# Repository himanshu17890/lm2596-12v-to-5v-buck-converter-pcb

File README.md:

# LM2596 12 V to 5 V Buck Converter PCB

A two-layer PCB for converting a 12 V DC input into a regulated 5 V DC output using an LM2596S-5 switching regulator.

## Features

- 12 V DC input through a 2-pin screw terminal
- Fixed 5 V DC output through a 2-pin screw terminal
- LM2596S-5 buck regulator
- Up to 3 A regulator rating; final usable current depends on cooling, copper area, and component ratings
- Two-layer layout with F.Cu and B.Cu ground pours
- Two M2 mounting holes and rounded board corners

## Connections

| Terminal | Pin 1 | Pin 2 |
|---|---|---|
| J3 input | IN+ / +12 V | IN- / GND |
| J4 output | OUT+ / +5 V | OUT- / GND |

Use DC input only. Do **not** connect AC mains. Confirm the output is approximately 5.0 V with a multimeter before connecting a load, and never reverse the input polarity.

## Main Components

| Reference | Component | Value / requirement |
|---|---|---|
| U1 | LM2596S-5 | Fixed 5 V buck regulator, TO-263-5 package |
| C1 | Polarized electrolytic capacitor | 680 uF, 25 V |
| C2 | Low-ESR polarized electrolytic capacitor | 220 uF, 10 V |
| L1 | Power inductor | 33 uH, at least 3 A saturation current |
| D1 | Schottky diode | 1N5824 or equivalent |
| J3, J4 | Screw terminals | 2-pin, 5.00 mm pitch |

## Project Files

Place the KiCad files in this repository root:

- `LM2596_Buck_Converter.kicad_pro`
- `LM2596_Buck_Converter.kicad_sch`
- `LM2596_Buck_Converter.kicad_pcb`

## Simulation

The design was verified in KiCad's built-in ngspice simulator using Texas Instruments' official transient SPICE model for the LM2596-5.0 (`LM2596_5P0_TRANS.LIB`, released by TI's Analog eLab Design Center), loaded via U1's Simulation Model dialog in place of a generic model.

**Setup:** 12 V input, 33 uH inductor, 220 uF output capacitor, 5 ohm (1 A) resistive load. Transient analysis, 50 ns time step, initial conditions enabled (`uic`) so the simulation starts from 0 V rather than an artificial DC operating point.

**Startup and settling — output ramps from 0 V through a stepped soft-start to ~5.0 V in about 1 ms:**

**Zoomed output ripple (3.25-3.41 ms window):**

**Results:**

- Output regulates to **~5.0 V**, matching the datasheet's 4.8-5.2 V spec at this load.
- Soft-start ramp from 0 V to regulation in **~1 ms**, matching the LM2596's internal soft-start behavior.
- With an ideal (zero-ESR) output capacitor, the loop rings at roughly 15 kHz with ~80 mV peak-to-peak swing, as shown above. Adding a realistic ESR of 0.05-0.1 ohm in series with C2 (representative of a genuine low-ESR electrolytic) damps this to **~20 mV**, confirming the datasheet's note that very low output-capacitor ESR can destabilize the feedback loop.

- 

**Model file:** [`sim/LM2596_5P0_TRANS.LIB`](sim/LM2596_5P0_TRANS.LIB)
See [`sim/SIMULATION_RESULTS.md`](sim/SIMULATION_RESULTS.md) for the full write-up, pin mapping, and settings.

> The model is TI's own release, provided "as is" with no warranty (see header comments in the file). It is not officially validated for ngspice, but ran without errors under ngspice's PSpice/LTspice compatibility mode.

## Manufacturing Checklist

1. Run ERC and DRC with zero errors.
2. Inspect the board in KiCad 3D Viewer.
3. Verify diode polarity, capacitor polarity, connector labels, and U1 orientation.
4. Verify every selected footprint matches the purchased component datasheet.
5. Generate Gerber and drill files from KiCad's Plot dialog.

## License

This project is provided for learning and personal use. Review the design independently before manufacturing or using it with valuable equipment.

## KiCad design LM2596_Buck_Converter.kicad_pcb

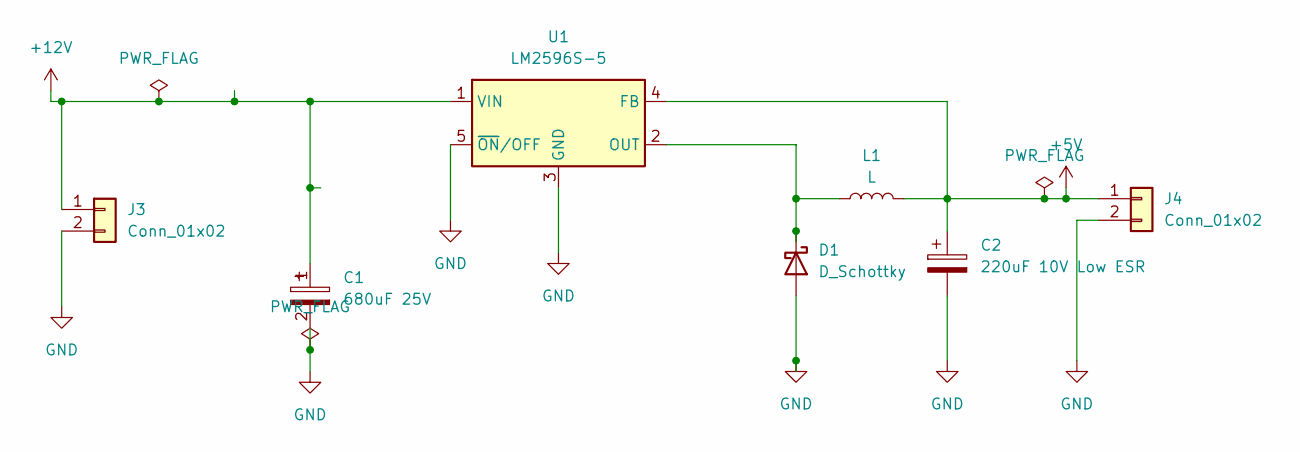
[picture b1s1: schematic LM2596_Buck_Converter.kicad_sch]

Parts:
C1: 680uF 25V; CP_Radial_D10.0mm_P5.00mm
C2: 220uF 10V Low ESR; CP_Radial_D8.0mm_P3.50mm
D1: D_Schottky; D_DO-201AD_P15.24mm_Horizontal
J3, J4: Conn_01x02; TerminalBlock_Phoenix_MKDS-1,5-2_1x02_P5.00mm_Horizontal
L1: L; L_Bourns_SRR1260
U1: LM2596S-5; TO-263-5_TabPin3

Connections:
+5V: C2.1, J4.1, L1.2, U1.4 (FB)
+12V: C1.1, J3.1, U1.1 (VIN)
GND: C1.2, C2.2, D1.2 (A), J3.2, J4.2, U1.3 (GND), U1.5 (~ON/OFF)
unnamed: D1.1 (K), L1.1, U1.2 (OUT)

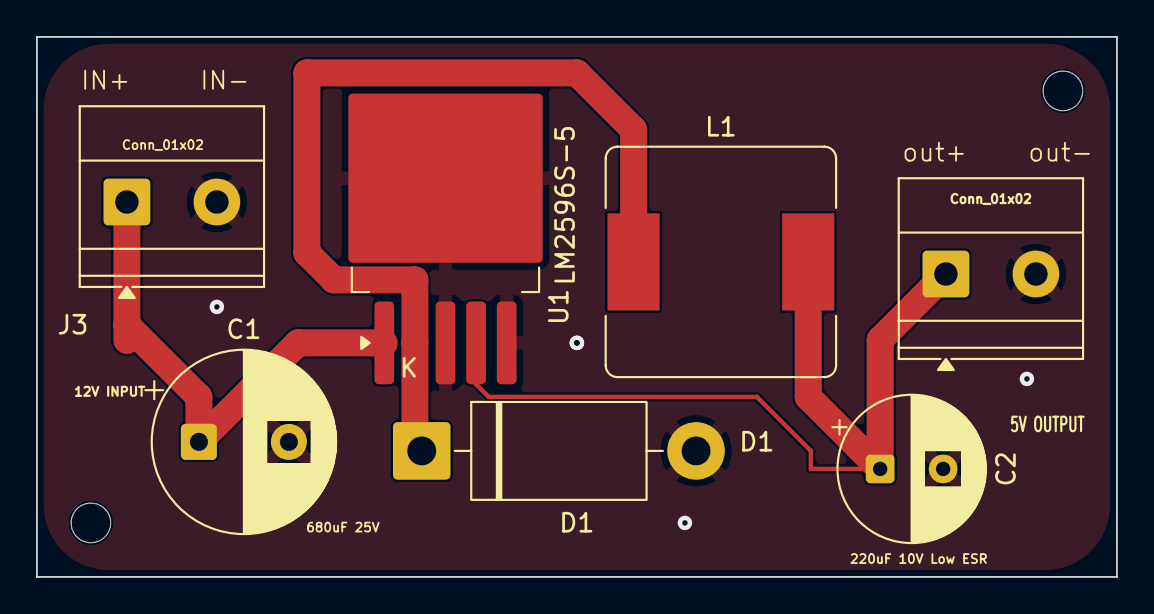
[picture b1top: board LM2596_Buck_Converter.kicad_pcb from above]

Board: 2 copper layers, 60.0 x 30.0 mm, 7 parts (0 on the bottom side), 4 nets.
